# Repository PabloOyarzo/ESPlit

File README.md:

---
{}
---
# ESPlit

The ESPlit is an Ergonomic Split Keyboard based on the ESP32. Uses CHOC style switches, LiPo Battery and I2C connection through QWIC and TRRS connectors. 

[v0.2-alpha - KICAD Web view from KiCanvas](https://kicanvas.org/?github=https://github.com/PabloOyarzo/ESPlit/blob/f03de27275e5d2c74a1ab2e2412ca9cb5b31ff47/split_keyboard.kicad_pro)

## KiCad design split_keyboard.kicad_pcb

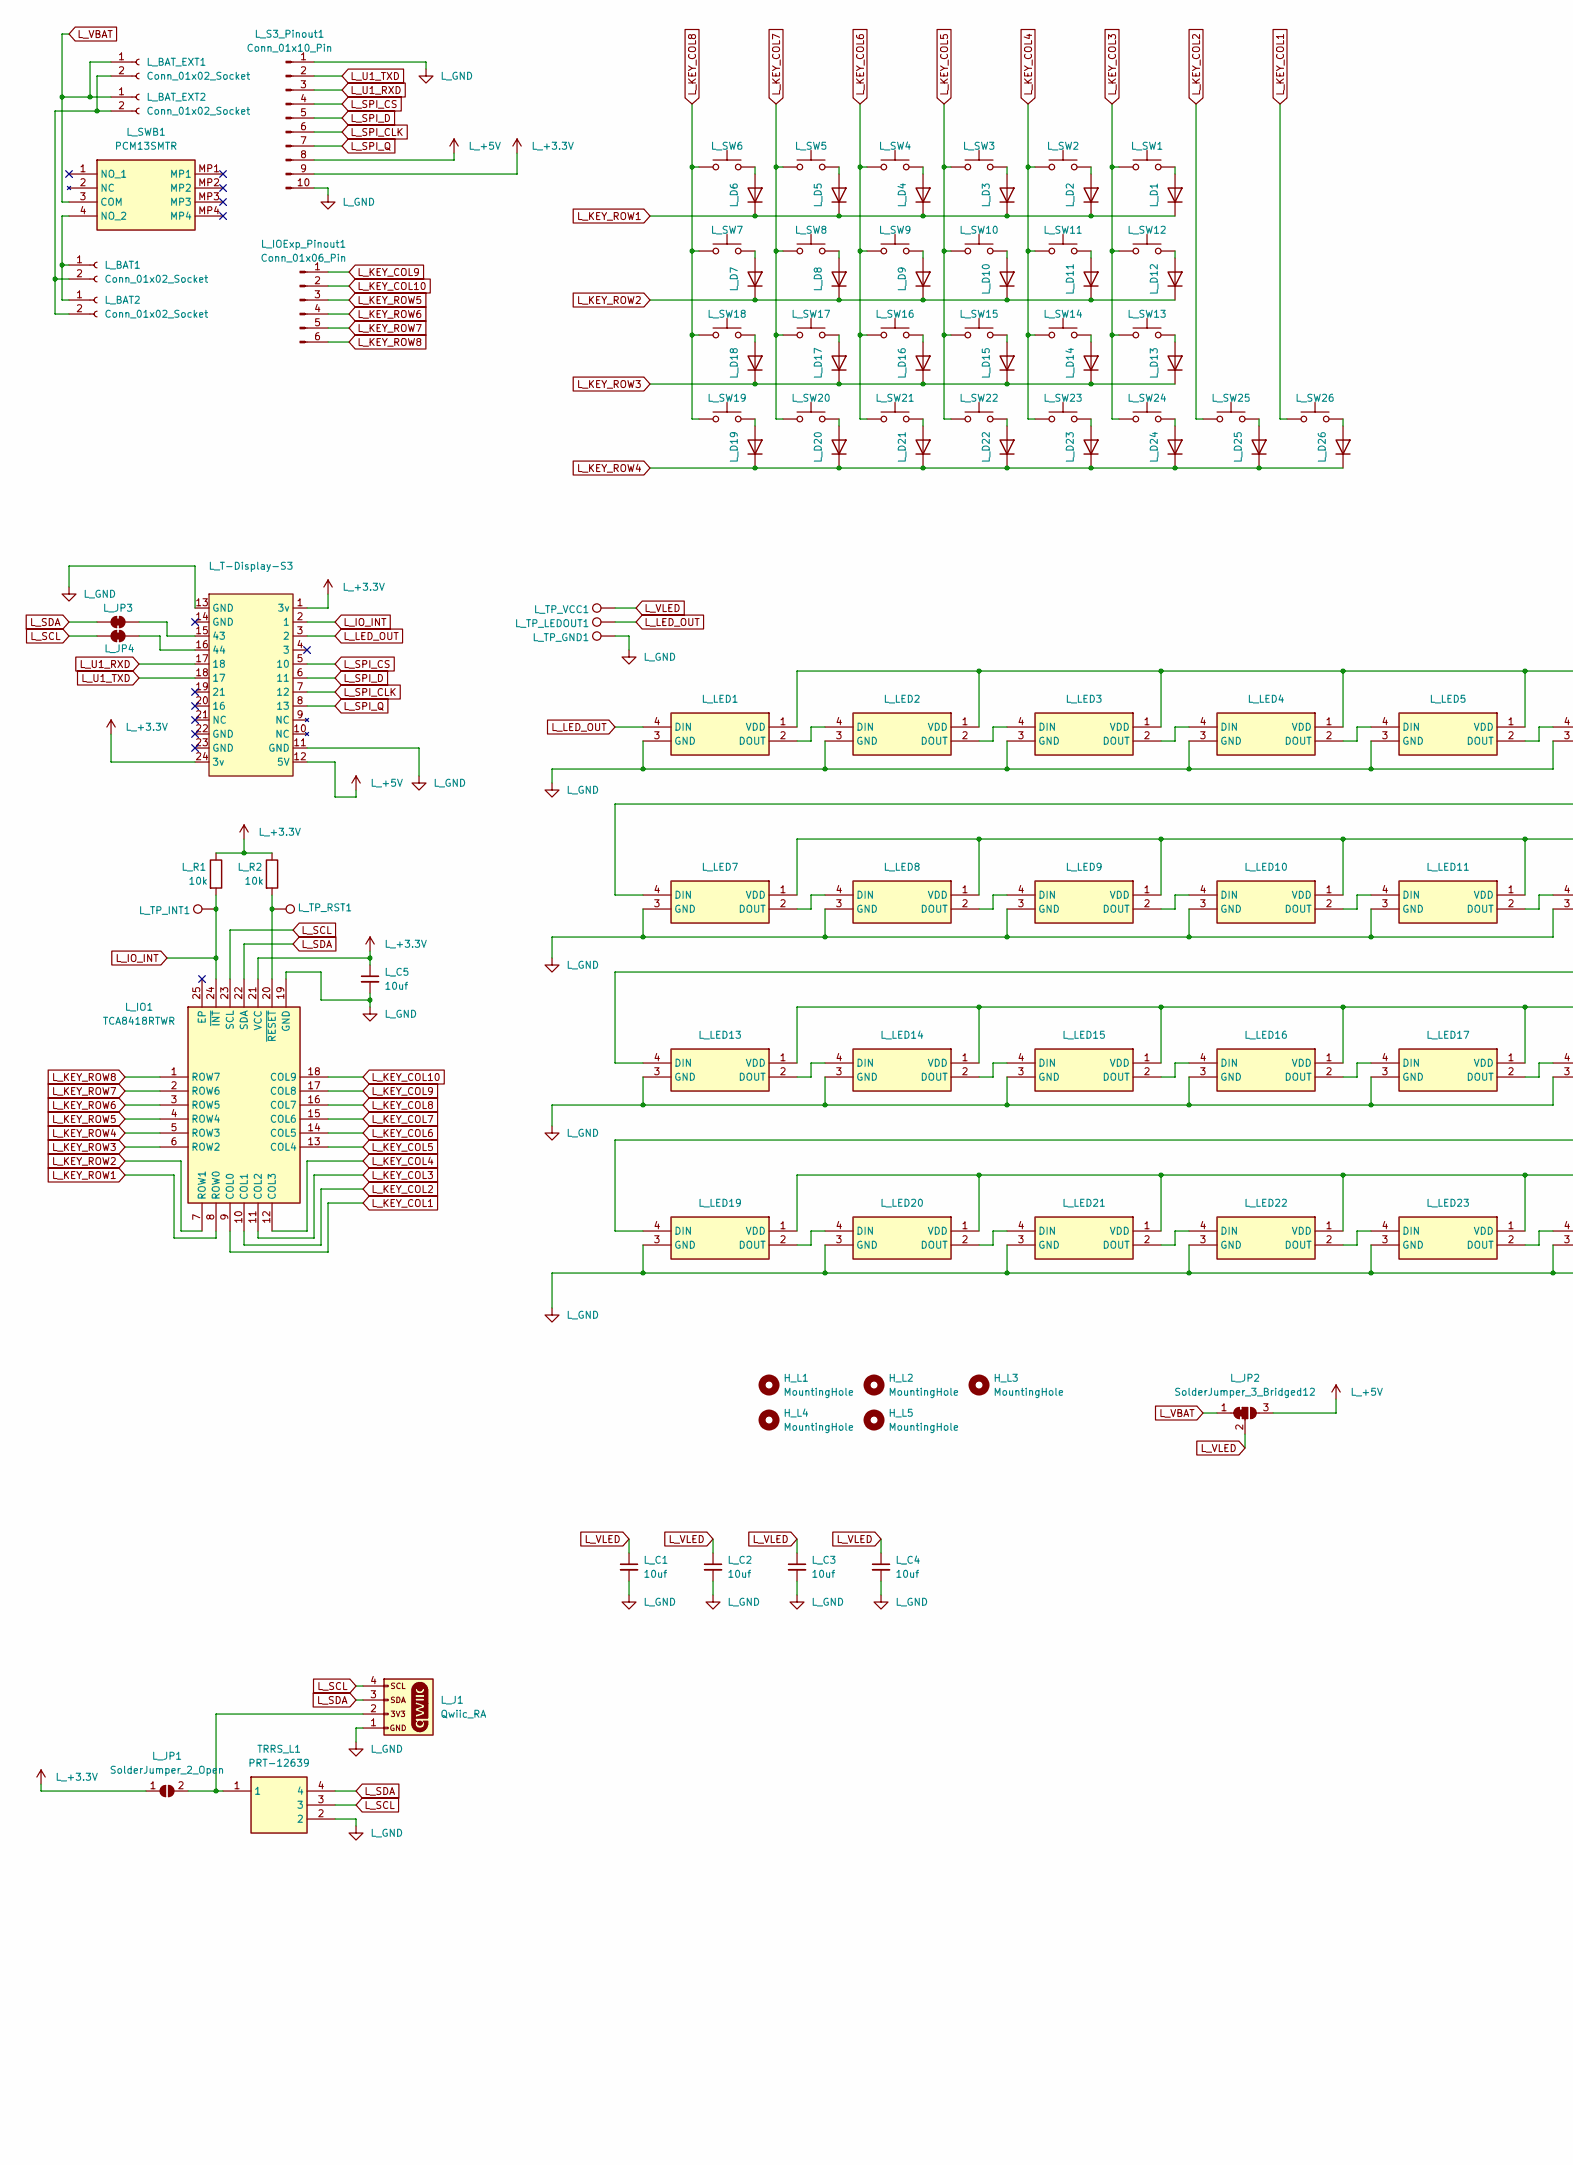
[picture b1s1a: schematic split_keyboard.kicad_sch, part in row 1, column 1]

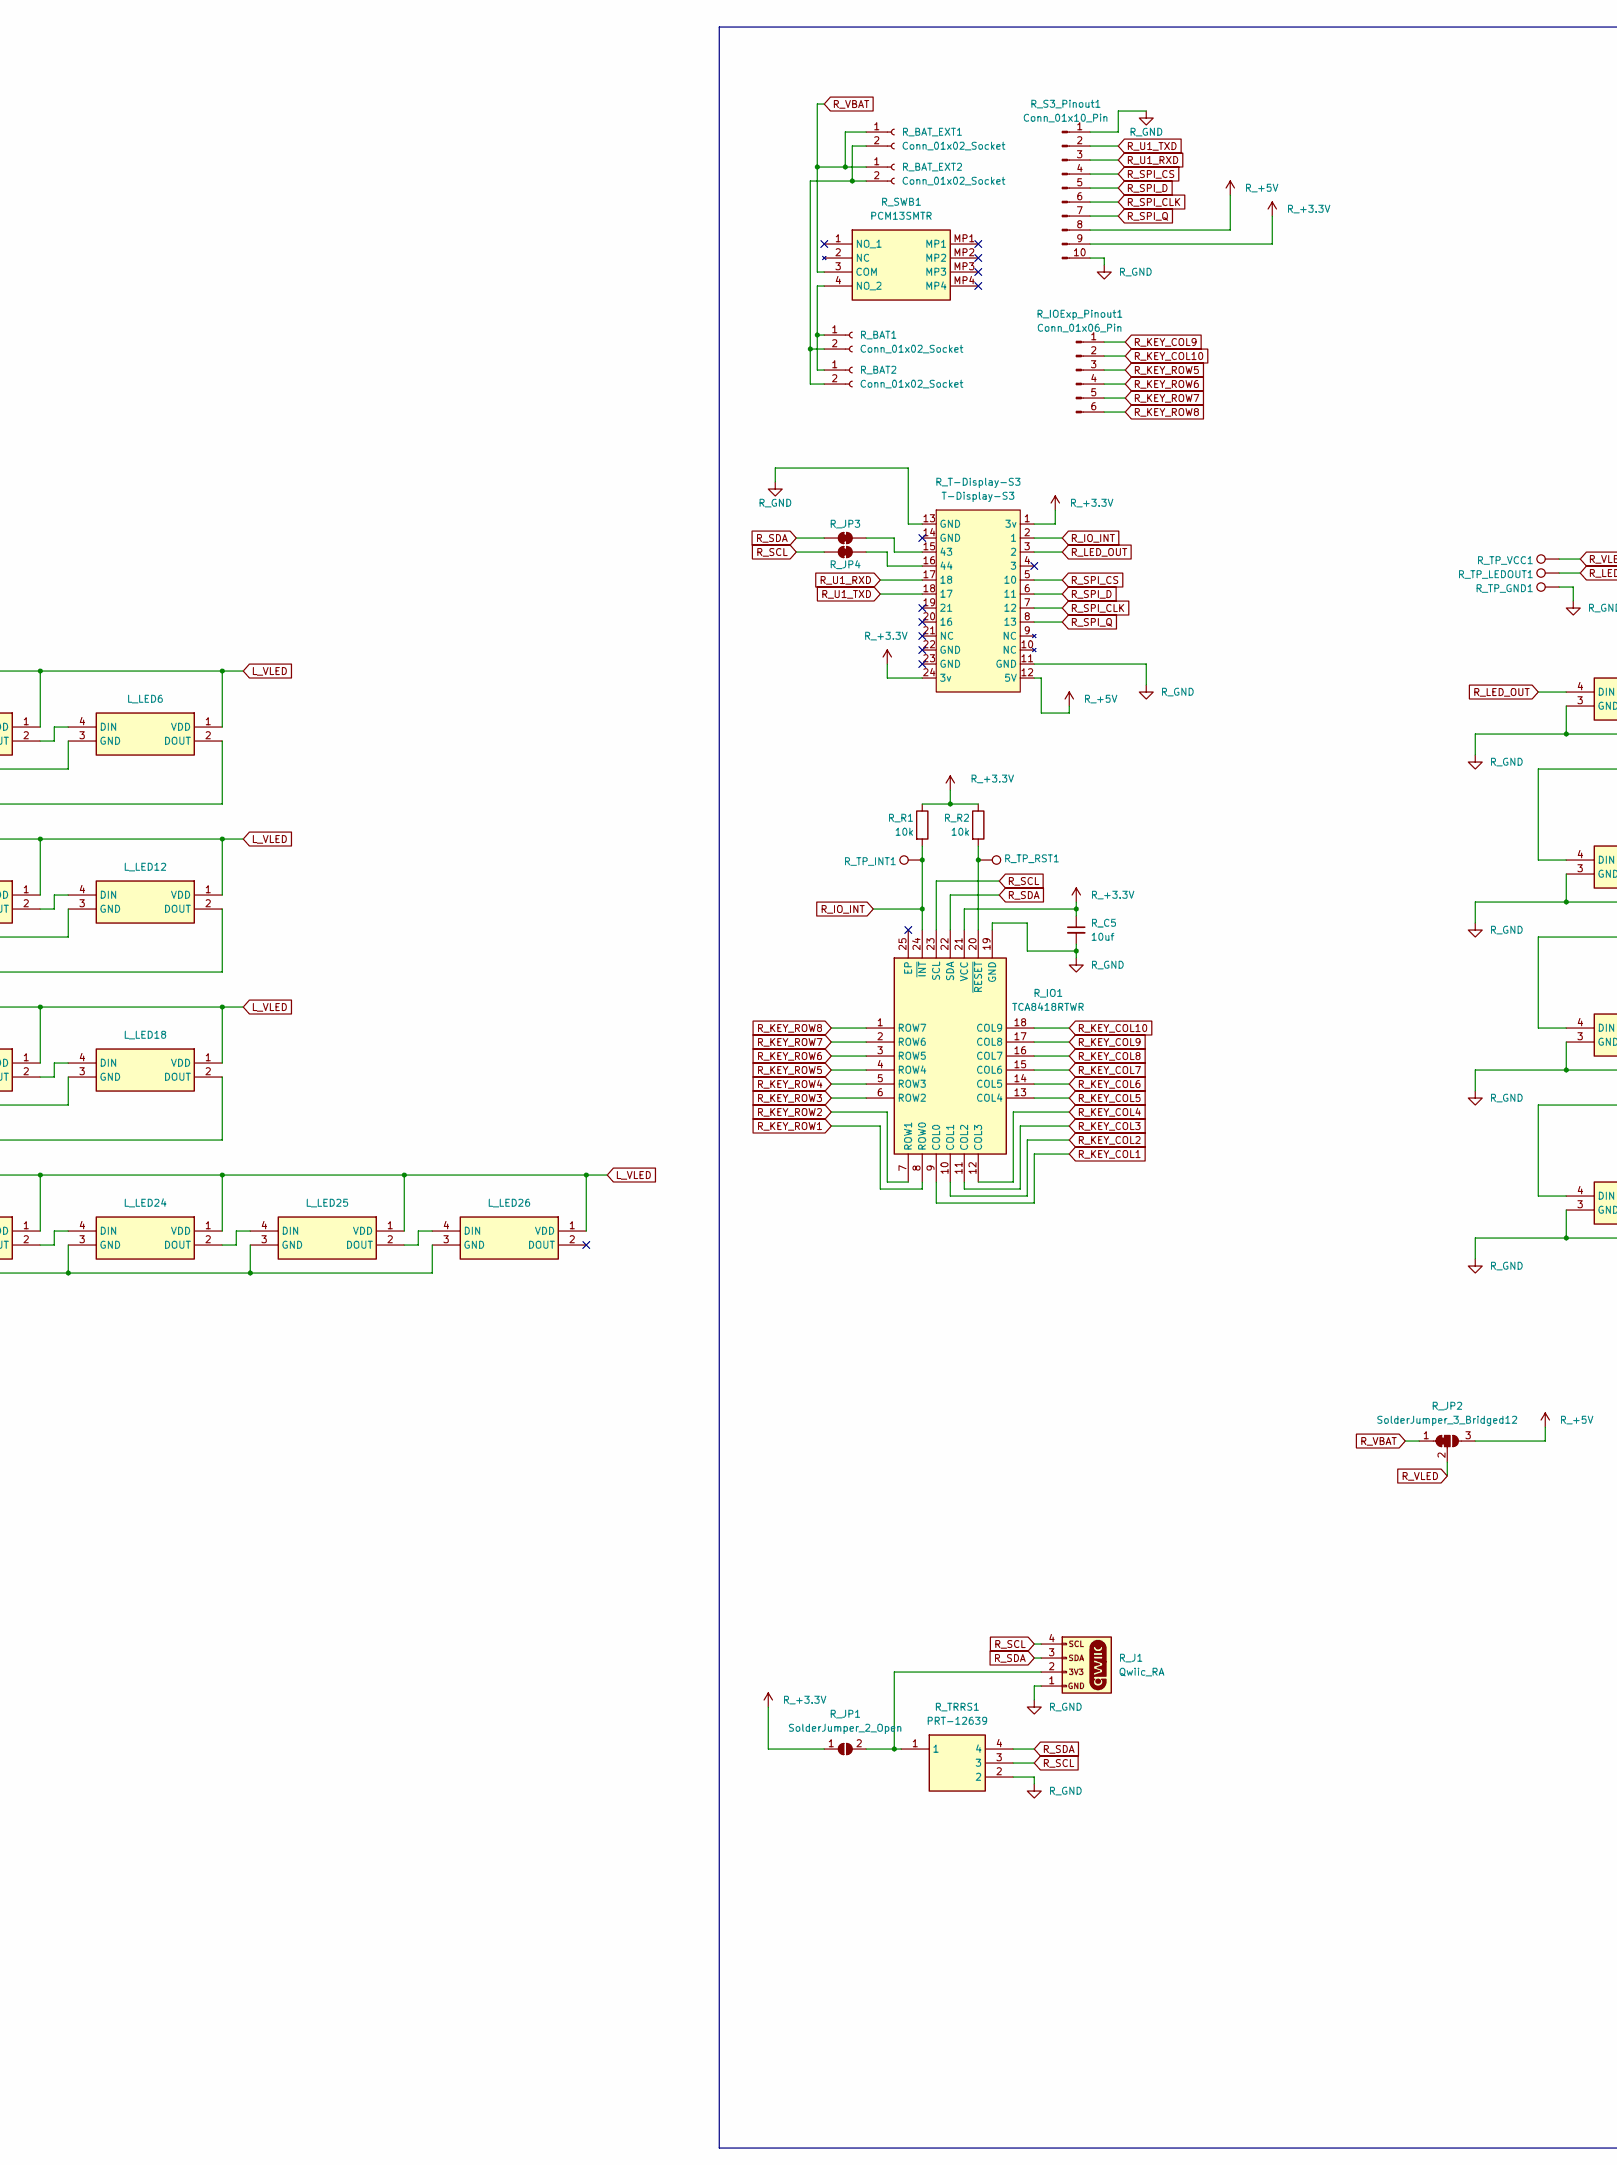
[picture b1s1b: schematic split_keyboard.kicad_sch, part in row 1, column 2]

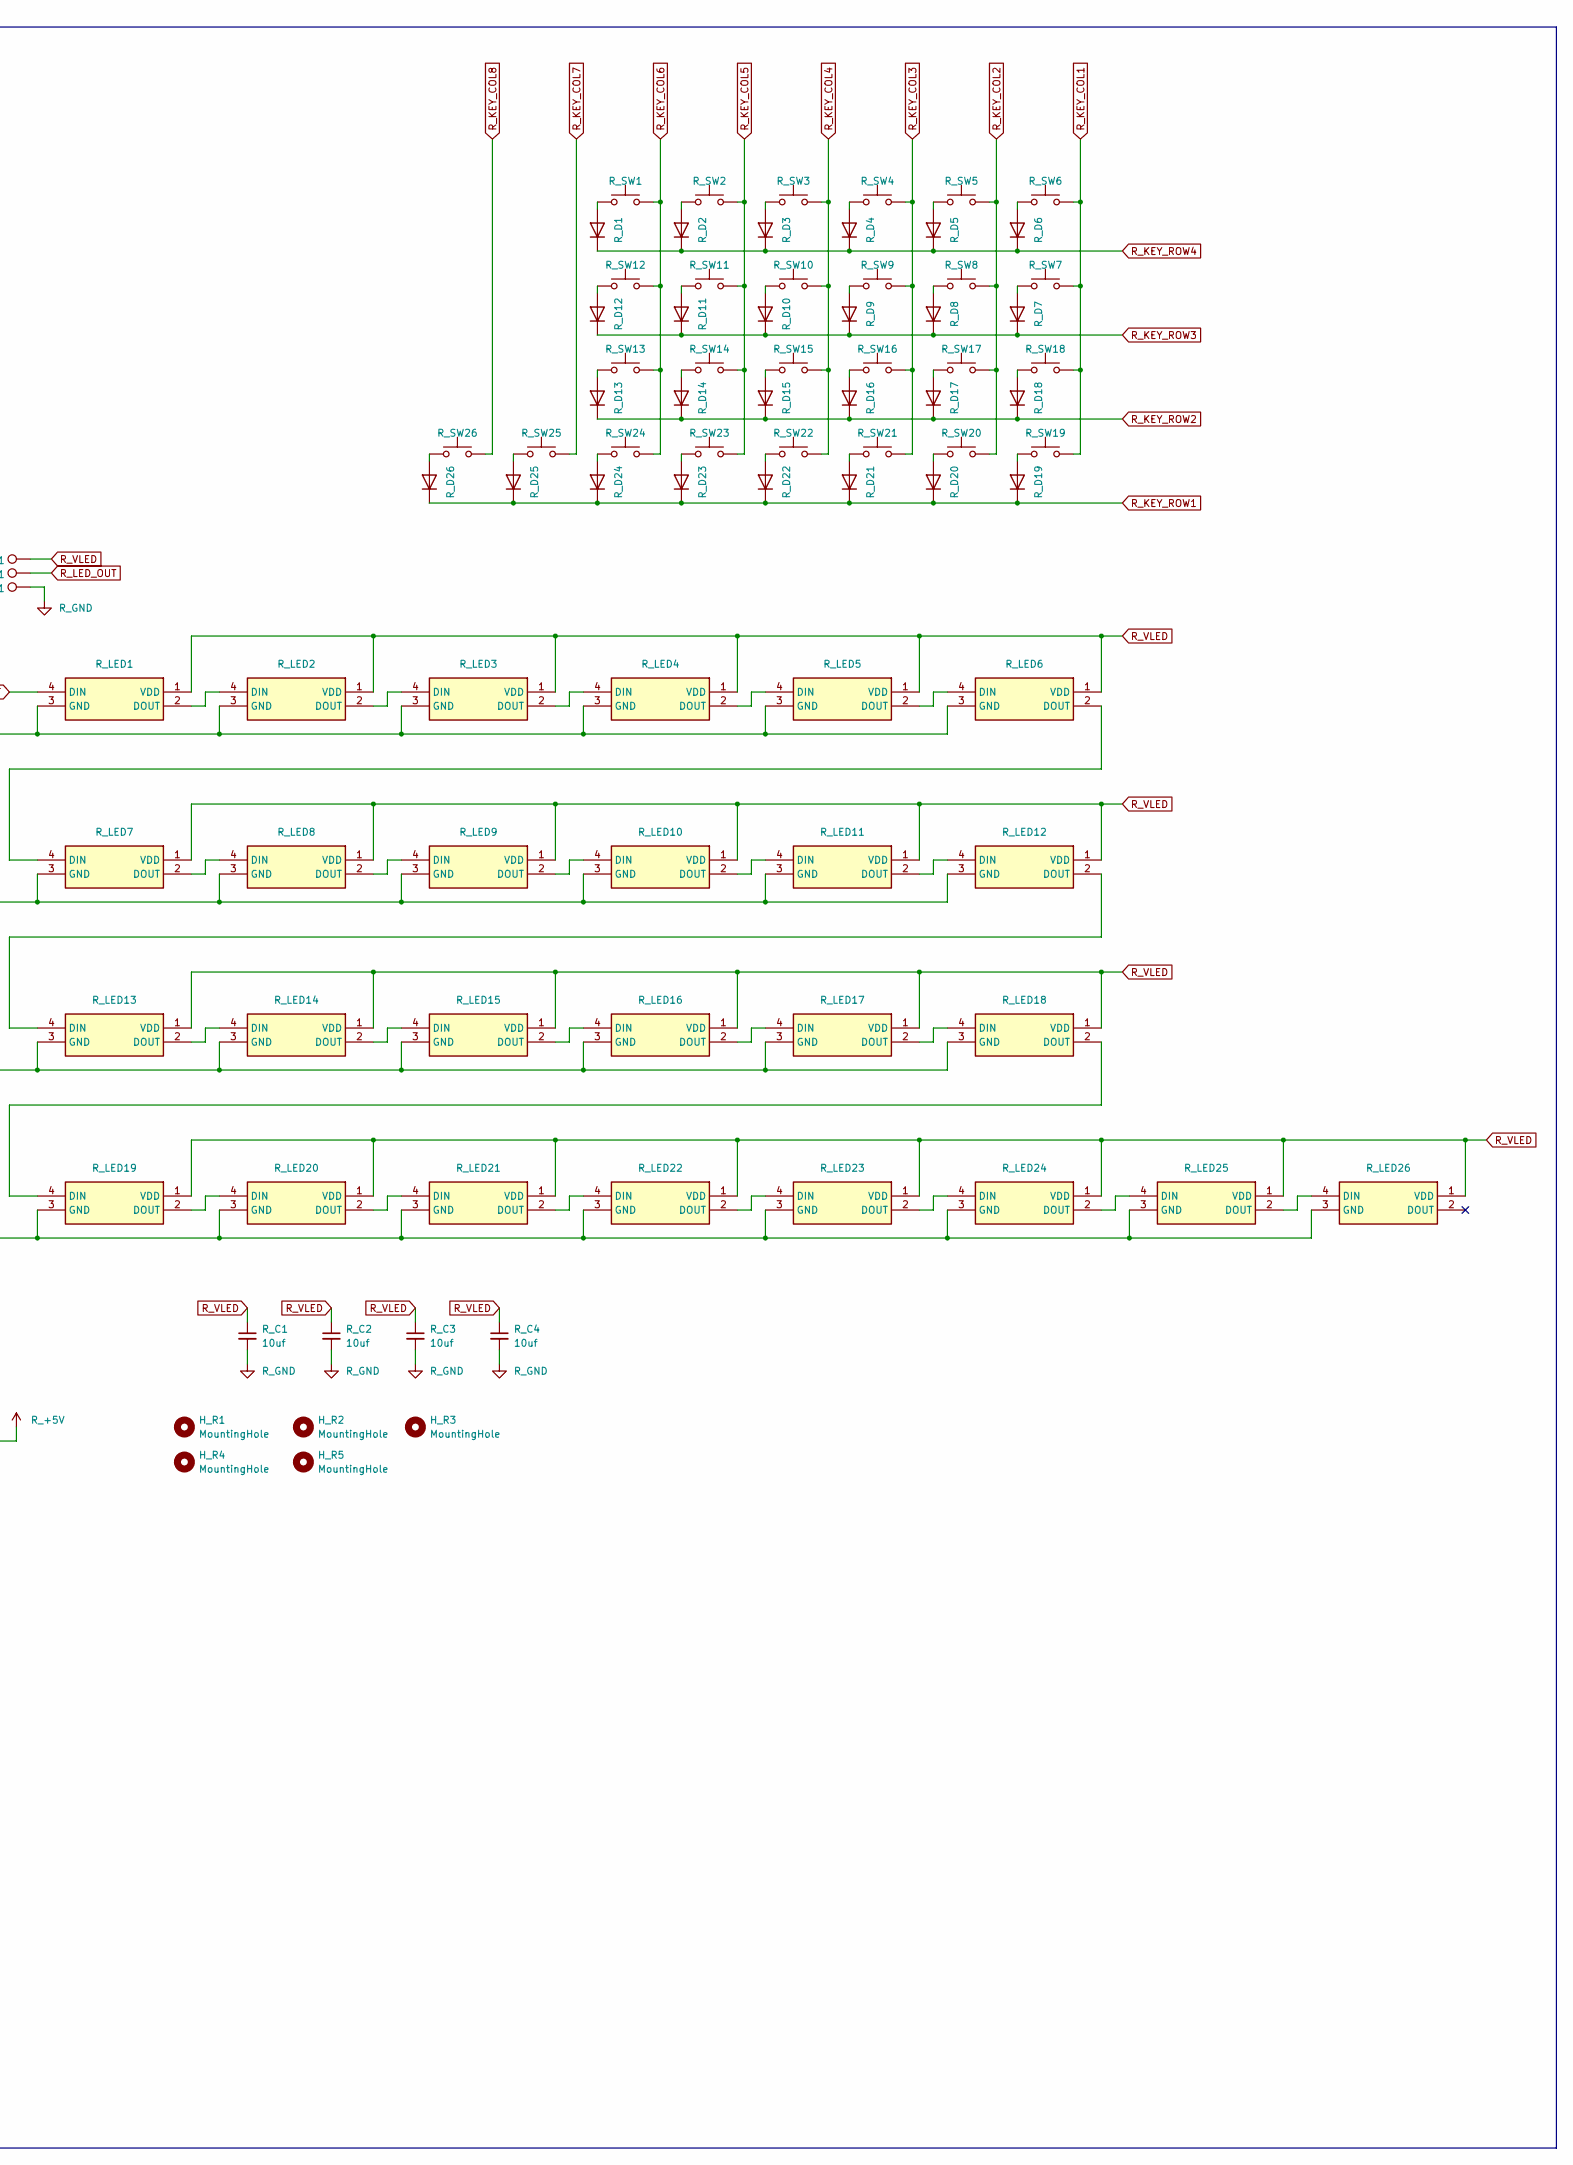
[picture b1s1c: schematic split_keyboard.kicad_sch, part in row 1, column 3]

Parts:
H_L1, H_L2, H_L3, H_L4, H_L5: MountingHole; MountingHole_2.5mm_Pad_TopBottom
H_R1, H_R2, H_R3, H_R4, H_R5: MountingHole; MountingHole_2.5mm_Pad_TopBottom
L_BAT1: Conn_01x02_Socket; JST_PH_B2B-PH-SM4-TB_02x2.00mm_Straight
L_BAT2: Conn_01x02_Socket; JST_GH_BM02B-GHS-TBT_02x1.25mm_Straight
L_BAT_EXT1: Conn_01x02_Socket; JST_PH_B2B-PH-SM4-TB_02x2.00mm_Straight
L_BAT_EXT2: Conn_01x02_Socket; PinHeader_1x02_P2.54mm_Vertical
L_C1, L_C2, L_C3, L_C4, L_C5: 10uf; C_0805_2012Metric
L_D1, L_D2, L_D3, L_D4, L_D5, L_D6, L_D7, L_D8, L_D9, L_D10, L_D11, L_D12, L_D13, L_D14, L_D15, L_D16, L_D17, L_D18, L_D19, L_D20, L_D21, L_D22, L_D23, L_D24, L_D25, L_D26: D; D_0805
L_IO1: TCA8418RTWR; QFN50P400X400X80-25N; Manufacturer_Part_Number TCA8418RTWR
L_IOExp_Pinout1: Conn_01x06_Pin; PinHeader_1x06_P2.54mm_Vertical
L_J1: Qwiic_RA; JST_SMD_1.0mm-4_RA
L_JP1: SolderJumper_2_Open; SolderJumper-2_P1.3mm_Open_TrianglePad1.0x1.5mm
L_JP2: SolderJumper_3_Bridged12; SolderJumper-3_P1.3mm_Bridged12_RoundedPad1.0x1.5mm
L_JP3, L_JP4: Measure; Jumper_2_NC_Trace_NoSilk
L_LED1, L_LED2, L_LED3, L_LED4, L_LED5, L_LED6, L_LED7, L_LED8, L_LED9, L_LED10, L_LED11, L_LED12, L_LED13, L_LED14, L_LED15, L_LED16, L_LED17, L_LED18, L_LED19, L_LED20, L_LED21, L_LED22, L_LED23, L_LED24, L_LED25, L_LED26: SK6812MINI-E; SK6812-MINI-E; Manufacturer_Part_Number SK6812MINI-E
L_R1, L_R2: 10k; R_0805_2012Metric
L_S3_Pinout1: Conn_01x10_Pin; PinHeader_1x10_P2.54mm_Vertical
L_SW1, L_SW2, L_SW3, L_SW4, L_SW5, L_SW6, L_SW7, L_SW8, L_SW9, L_SW10, L_SW11, L_SW12, L_SW13, L_SW14, L_SW15, L_SW16, L_SW17, L_SW18, L_SW19, L_SW20, L_SW21, L_SW22, L_SW23, L_SW24, L_SW25, L_SW26: L_SW; SW_Hotswap_Kailh_Choc_V1V2_Plated_1.00u
L_SWB1: PCM13SMTR; Manufacturer_Part_Number PCM13SMTR
L_T-Display-S3: T-Display-S3
L_TP_GND1: 1.25mm; TestPoint-1.25mm
L_TP_INT1: 1.25mm; TestPoint-1.25mm
L_TP_LEDOUT1: 1.25mm; TestPoint-1.25mm
L_TP_RST1: 1.25mm; TestPoint-1.25mm
L_TP_VCC1: 1.25mm; TestPoint-1.25mm
R_BAT1: Conn_01x02_Socket; JST_PH_B2B-PH-SM4-TB_02x2.00mm_Straight
R_BAT2: Conn_01x02_Socket; JST_GH_BM02B-GHS-TBT_02x1.25mm_Straight
R_BAT_EXT1: Conn_01x02_Socket; JST_PH_B2B-PH-SM4-TB_02x2.00mm_Straight
R_BAT_EXT2: Conn_01x02_Socket; PinHeader_1x02_P2.54mm_Vertical
R_C1, R_C2, R_C3, R_C4, R_C5: 10uf; C_0805_2012Metric
R_D1, R_D2, R_D3, R_D4, R_D5, R_D6, R_D7, R_D8, R_D9, R_D10, R_D11, R_D12, R_D13, R_D14, R_D15, R_D16, R_D17, R_D18, R_D19, R_D20, R_D21, R_D22, R_D23, R_D24, R_D25, R_D26: D; D_0805
R_IO1: TCA8418RTWR; QFN50P400X400X80-25N; Manufacturer_Part_Number TCA8418RTWR
R_IOExp_Pinout1: Conn_01x06_Pin; PinHeader_1x06_P2.54mm_Vertical
R_J1: Qwiic_RA; JST_SMD_1.0mm-4_RA
R_JP1: SolderJumper_2_Open; SolderJumper-2_P1.3mm_Open_TrianglePad1.0x1.5mm
R_JP2: SolderJumper_3_Bridged12; SolderJumper-3_P1.3mm_Bridged12_RoundedPad1.0x1.5mm
R_JP3, R_JP4: Measure; Jumper_2_NC_Trace_NoSilk
R_LED1, R_LED2, R_LED3, R_LED4, R_LED5, R_LED6, R_LED7, R_LED8, R_LED9, R_LED10, R_LED11, R_LED12, R_LED13, R_LED14, R_LED15, R_LED16, R_LED17, R_LED18, R_LED19, R_LED20, R_LED21, R_LED22, R_LED23, R_LED24, R_LED25, R_LED26: SK6812MINI-E; SK6812-MINI-E; Manufacturer_Part_Number SK6812MINI-E
R_R1, R_R2: 10k; R_0805_2012Metric
R_S3_Pinout1: Conn_01x10_Pin; PinHeader_1x10_P2.54mm_Vertical
R_SW1, R_SW2, R_SW3, R_SW4, R_SW5, R_SW6, R_SW7, R_SW8, R_SW9, R_SW10, R_SW11, R_SW12, R_SW13, R_SW14, R_SW15, R_SW16, R_SW17, R_SW18, R_SW19, R_SW20, R_SW21, R_SW22, R_SW23, R_SW24, R_SW25, R_SW26: L_SW; SW_Hotswap_Kailh_Choc_V1V2_Plated_1.00u
R_SWB1: PCM13SMTR; Manufacturer_Part_Number PCM13SMTR
R_T-Display-S3: T-Display-S3
R_TP_GND1: 1.25mm; TestPoint-1.25mm
R_TP_INT1: 1.25mm; TestPoint-1.25mm
R_TP_LEDOUT1: 1.25mm; TestPoint-1.25mm
R_TP_RST1: 1.25mm; TestPoint-1.25mm
R_TP_VCC1: 1.25mm; TestPoint-1.25mm
R_TRRS1: PRT-12639; TRRS-PJ-320A; Manufacturer_Part_Number PRT-12639
TRRS_L1: PRT-12639; TRRS-PJ-320A; Manufacturer_Part_Number PRT-12639

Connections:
L_+3.3V: L_C5.1, L_IO1.21 (VCC), L_JP1.1 (A), L_R1.1, L_R2.1, L_S3_Pinout1.9, L_T-Display-S3.1 (3v), L_T-Display-S3.24 (3v)
L_+5V: L_JP2.3 (B), L_S3_Pinout1.8, L_T-Display-S3.12 (5V)
L_GND: L_C1.2, L_C2.2, L_C3.2, L_C4.2, L_C5.2, L_IO1.19 (GND), L_J1.1, L_LED1.3 (GND), L_LED2.3 (GND), L_LED3.3 (GND), L_LED4.3 (GND), L_LED5.3 (GND), L_LED6.3 (GND), L_LED7.3 (GND), L_LED8.3 (GND), L_LED9.3 (GND), L_LED10.3 (GND), L_LED11.3 (GND), L_LED12.3 (GND), L_LED13.3 (GND), L_LED14.3 (GND), L_LED15.3 (GND), L_LED16.3 (GND), L_LED17.3 (GND), L_LED18.3 (GND), L_LED19.3 (GND), L_LED20.3 (GND), L_LED21.3 (GND), L_LED22.3 (GND), L_LED23.3 (GND), L_LED24.3 (GND), L_LED25.3 (GND), L_LED26.3 (GND), L_S3_Pinout1.1, L_S3_Pinout1.10, L_T-Display-S3.11 (GND), L_T-Display-S3.13 (GND), L_TP_GND1.1, TRRS_L1.2
L_IO_INT: L_IO1.24 (~INT), L_R1.2, L_T-Display-S3.2 (1), L_TP_INT1.1
L_KEY_COL1: L_IO1.9 (COL0), L_SW26.1
L_KEY_COL2: L_IO1.10 (COL1), L_SW25.1
L_KEY_COL3: L_IO1.11 (COL2), L_SW1.1, L_SW12.1, L_SW13.1, L_SW24.1
L_KEY_COL4: L_IO1.12 (COL3), L_SW2.1, L_SW11.1, L_SW14.1, L_SW23.1
L_KEY_COL5: L_IO1.13 (COL4), L_SW3.1, L_SW10.1, L_SW15.1, L_SW22.1
L_KEY_COL6: L_IO1.14 (COL5), L_SW4.1, L_SW9.1, L_SW16.1, L_SW21.1
L_KEY_COL7: L_IO1.15 (COL6), L_SW5.1, L_SW8.1, L_SW17.1, L_SW20.1
L_KEY_COL8: L_IO1.16 (COL7), L_SW6.1, L_SW7.1, L_SW18.1, L_SW19.1
L_KEY_COL9: L_IO1.17 (COL8), L_IOExp_Pinout1.1
L_KEY_COL10: L_IO1.18 (COL9), L_IOExp_Pinout1.2
L_KEY_ROW1: L_D1.1 (K), L_D2.1 (K), L_D3.1 (K), L_D4.1 (K), L_D5.1 (K), L_D6.1 (K), L_IO1.8 (ROW0)
L_KEY_ROW2: L_D7.1 (K), L_D8.1 (K), L_D9.1 (K), L_D10.1 (K), L_D11.1 (K), L_D12.1 (K), L_IO1.7 (ROW1)
L_KEY_ROW3: L_D13.1 (K), L_D14.1 (K), L_D15.1 (K), L_D16.1 (K), L_D17.1 (K), L_D18.1 (K), L_IO1.6 (ROW2)
L_KEY_ROW4: L_D19.1 (K), L_D20.1 (K), L_D21.1 (K), L_D22.1 (K), L_D23.1 (K), L_D24.1 (K), L_D25.1 (K), L_D26.1 (K), L_IO1.5 (ROW3)
L_KEY_ROW5: L_IO1.4 (ROW4), L_IOExp_Pinout1.3
L_KEY_ROW6: L_IO1.3 (ROW5), L_IOExp_Pinout1.4
L_KEY_ROW7: L_IO1.2 (ROW6), L_IOExp_Pinout1.5
L_KEY_ROW8: L_IO1.1 (ROW7), L_IOExp_Pinout1.6
L_LED_OUT: L_LED1.4 (DIN), L_T-Display-S3.3 (2), L_TP_LEDOUT1.1
L_SCL: L_IO1.23 (SCL), L_J1.4, L_JP4.1 (A), TRRS_L1.3
L_SDA: L_IO1.22 (SDA), L_J1.3, L_JP3.1 (A), TRRS_L1.4
L_SPI_CLK: L_S3_Pinout1.6, L_T-Display-S3.7 (12)
L_SPI_CS: L_S3_Pinout1.4, L_T-Display-S3.5 (10)
L_SPI_D: L_S3_Pinout1.5, L_T-Display-S3.6 (11)
L_SPI_Q: L_S3_Pinout1.7, L_T-Display-S3.8 (13)
L_U1_RXD: L_S3_Pinout1.3, L_T-Display-S3.17 (18)
L_U1_TXD: L_S3_Pinout1.2, L_T-Display-S3.18 (17)
L_VBAT: L_BAT_EXT1.1, L_BAT_EXT2.1, L_JP2.1 (A), L_SWB1.3 (COM)
L_VLED: L_C1.1, L_C2.1, L_C3.1, L_C4.1, L_JP2.2 (C), L_LED1.1 (VDD), L_LED2.1 (VDD), L_LED3.1 (VDD), L_LED4.1 (VDD), L_LED5.1 (VDD), L_LED6.1 (VDD), L_LED7.1 (VDD), L_LED8.1 (VDD), L_LED9.1 (VDD), L_LED10.1 (VDD), L_LED11.1 (VDD), L_LED12.1 (VDD), L_LED13.1 (VDD), L_LED14.1 (VDD), L_LED15.1 (VDD), L_LED16.1 (VDD), L_LED17.1 (VDD), L_LED18.1 (VDD), L_LED19.1 (VDD), L_LED20.1 (VDD), L_LED21.1 (VDD), L_LED22.1 (VDD), L_LED23.1 (VDD), L_LED24.1 (VDD), L_LED25.1 (VDD), L_LED26.1 (VDD), L_TP_VCC1.1
unnamed: L_BAT1.1, L_BAT2.1, L_SWB1.4 (NO_2)
unnamed: L_BAT1.2, L_BAT2.2, L_BAT_EXT1.2, L_BAT_EXT2.2
unnamed: L_D1.2 (A), L_SW1.2
unnamed: L_D2.2 (A), L_SW2.2
unnamed: L_D3.2 (A), L_SW3.2
unnamed: L_D4.2 (A), L_SW4.2
unnamed: L_D5.2 (A), L_SW5.2
unnamed: L_D6.2 (A), L_SW6.2
unnamed: L_D7.2 (A), L_SW7.2
unnamed: L_D8.2 (A), L_SW8.2
unnamed: L_D9.2 (A), L_SW9.2
unnamed: L_D10.2 (A), L_SW10.2
unnamed: L_D11.2 (A), L_SW11.2
unnamed: L_D12.2 (A), L_SW12.2
unnamed: L_D13.2 (A), L_SW13.2
unnamed: L_D14.2 (A), L_SW14.2
unnamed: L_D15.2 (A), L_SW15.2
unnamed: L_D16.2 (A), L_SW16.2
unnamed: L_D17.2 (A), L_SW17.2
unnamed: L_D18.2 (A), L_SW18.2
unnamed: L_D19.2 (A), L_SW19.2
unnamed: L_D20.2 (A), L_SW20.2
unnamed: L_D21.2 (A), L_SW21.2
unnamed: L_D22.2 (A), L_SW22.2
unnamed: L_D23.2 (A), L_SW23.2
unnamed: L_D24.2 (A), L_SW24.2
unnamed: L_D25.2 (A), L_SW25.2
unnamed: L_D26.2 (A), L_SW26.2
unnamed: L_IO1.20 (~RESET), L_R2.2, L_TP_RST1.1
unnamed: L_J1.2, L_JP1.2 (B), TRRS_L1.1
unnamed: L_JP3.2 (B), L_T-Display-S3.15 (43)
unnamed: L_JP4.2 (B), L_T-Display-S3.16 (44)
unnamed: L_LED1.2 (DOUT), L_LED2.4 (DIN)
unnamed: L_LED2.2 (DOUT), L_LED3.4 (DIN)
unnamed: L_LED3.2 (DOUT), L_LED4.4 (DIN)
unnamed: L_LED4.2 (DOUT), L_LED5.4 (DIN)
unnamed: L_LED5.2 (DOUT), L_LED6.4 (DIN)
unnamed: L_LED6.2 (DOUT), L_LED7.4 (DIN)
unnamed: L_LED7.2 (DOUT), L_LED8.4 (DIN)
unnamed: L_LED8.2 (DOUT), L_LED9.4 (DIN)
unnamed: L_LED9.2 (DOUT), L_LED10.4 (DIN)
unnamed: L_LED10.2 (DOUT), L_LED11.4 (DIN)
unnamed: L_LED11.2 (DOUT), L_LED12.4 (DIN)
unnamed: L_LED12.2 (DOUT), L_LED13.4 (DIN)
unnamed: L_LED13.2 (DOUT), L_LED14.4 (DIN)
unnamed: L_LED14.2 (DOUT), L_LED15.4 (DIN)
unnamed: L_LED15.2 (DOUT), L_LED16.4 (DIN)
unnamed: L_LED16.2 (DOUT), L_LED17.4 (DIN)
unnamed: L_LED17.2 (DOUT), L_LED18.4 (DIN)
unnamed: L_LED18.2 (DOUT), L_LED19.4 (DIN)
unnamed: L_LED19.2 (DOUT), L_LED20.4 (DIN)
unnamed: L_LED20.2 (DOUT), L_LED21.4 (DIN)
unnamed: L_LED21.2 (DOUT), L_LED22.4 (DIN)
unnamed: L_LED22.2 (DOUT), L_LED23.4 (DIN)
unnamed: L_LED23.2 (DOUT), L_LED24.4 (DIN)
unnamed: L_LED24.2 (DOUT), L_LED25.4 (DIN)
unnamed: L_LED25.2 (DOUT), L_LED26.4 (DIN)
unnamed: R_BAT1.1, R_BAT2.1, R_SWB1.4 (NO_2)
unnamed: R_BAT1.2, R_BAT2.2, R_BAT_EXT1.2, R_BAT_EXT2.2
unnamed: R_D1.2 (A), R_SW1.2
unnamed: R_D2.2 (A), R_SW2.2
unnamed: R_D3.2 (A), R_SW3.2
unnamed: R_D4.2 (A), R_SW4.2
unnamed: R_D5.2 (A), R_SW5.2
unnamed: R_D6.2 (A), R_SW6.2
unnamed: R_D7.2 (A), R_SW7.2
unnamed: R_D8.2 (A), R_SW8.2
unnamed: R_D9.2 (A), R_SW9.2
unnamed: R_D10.2 (A), R_SW10.2
unnamed: R_D11.2 (A), R_SW11.2
unnamed: R_D12.2 (A), R_SW12.2
unnamed: R_D13.2 (A), R_SW13.2
unnamed: R_D14.2 (A), R_SW14.2
unnamed: R_D15.2 (A), R_SW15.2
unnamed: R_D16.2 (A), R_SW16.2
unnamed: R_D17.2 (A), R_SW17.2
unnamed: R_D18.2 (A), R_SW18.2
unnamed: R_D19.2 (A), R_SW19.2
unnamed: R_D20.2 (A), R_SW20.2
unnamed: R_D21.2 (A), R_SW21.2
unnamed: R_D22.2 (A), R_SW22.2
unnamed: R_D23.2 (A), R_SW23.2
unnamed: R_D24.2 (A), R_SW24.2
unnamed: R_D25.2 (A), R_SW25.2
unnamed: R_D26.2 (A), R_SW26.2
unnamed: R_IO1.20 (~RESET), R_R2.2, R_TP_RST1.1
unnamed: R_J1.2, R_JP1.2 (B), R_TRRS1.1
unnamed: R_JP3.2 (B), R_T-Display-S3.15 (43)
unnamed: R_JP4.2 (B), R_T-Display-S3.16 (44)
unnamed: R_LED1.2 (DOUT), R_LED2.4 (DIN)
unnamed: R_LED2.2 (DOUT), R_LED3.4 (DIN)
unnamed: R_LED3.2 (DOUT), R_LED4.4 (DIN)
unnamed: R_LED4.2 (DOUT), R_LED5.4 (DIN)
unnamed: R_LED5.2 (DOUT), R_LED6.4 (DIN)
unnamed: R_LED6.2 (DOUT), R_LED7.4 (DIN)
unnamed: R_LED7.2 (DOUT), R_LED8.4 (DIN)
unnamed: R_LED8.2 (DOUT), R_LED9.4 (DIN)
unnamed: R_LED9.2 (DOUT), R_LED10.4 (DIN)
unnamed: R_LED10.2 (DOUT), R_LED11.4 (DIN)
unnamed: R_LED11.2 (DOUT), R_LED12.4 (DIN)
unnamed: R_LED12.2 (DOUT), R_LED13.4 (DIN)
unnamed: R_LED13.2 (DOUT), R_LED14.4 (DIN)
unnamed: R_LED14.2 (DOUT), R_LED15.4 (DIN)
unnamed: R_LED15.2 (DOUT), R_LED16.4 (DIN)
unnamed: R_LED16.2 (DOUT), R_LED17.4 (DIN)
unnamed: R_LED17.2 (DOUT), R_LED18.4 (DIN)
unnamed: R_LED18.2 (DOUT), R_LED19.4 (DIN)
unnamed: R_LED19.2 (DOUT), R_LED20.4 (DIN)
unnamed: R_LED20.2 (DOUT), R_LED21.4 (DIN)
unnamed: R_LED21.2 (DOUT), R_LED22.4 (DIN)
unnamed: R_LED22.2 (DOUT), R_LED23.4 (DIN)
unnamed: R_LED23.2 (DOUT), R_LED24.4 (DIN)
unnamed: R_LED24.2 (DOUT), R_LED25.4 (DIN)
unnamed: R_LED25.2 (DOUT), R_LED26.4 (DIN)
R_+3.3V: R_C5.1, R_IO1.21 (VCC), R_JP1.1 (A), R_R1.1, R_R2.1, R_S3_Pinout1.9, R_T-Display-S3.1 (3v), R_T-Display-S3.24 (3v)
R_+5V: R_JP2.3 (B), R_S3_Pinout1.8, R_T-Display-S3.12 (5V)
R_GND: R_C1.2, R_C2.2, R_C3.2, R_C4.2, R_C5.2, R_IO1.19 (GND), R_J1.1, R_LED1.3 (GND), R_LED2.3 (GND), R_LED3.3 (GND), R_LED4.3 (GND), R_LED5.3 (GND), R_LED6.3 (GND), R_LED7.3 (GND), R_LED8.3 (GND), R_LED9.3 (GND), R_LED10.3 (GND), R_LED11.3 (GND), R_LED12.3 (GND), R_LED13.3 (GND), R_LED14.3 (GND), R_LED15.3 (GND), R_LED16.3 (GND), R_LED17.3 (GND), R_LED18.3 (GND), R_LED19.3 (GND), R_LED20.3 (GND), R_LED21.3 (GND), R_LED22.3 (GND), R_LED23.3 (GND), R_LED24.3 (GND), R_LED25.3 (GND), R_LED26.3 (GND), R_S3_Pinout1.1, R_S3_Pinout1.10, R_T-Display-S3.11 (GND), R_T-Display-S3.13 (GND), R_TP_GND1.1, R_TRRS1.2
R_IO_INT: R_IO1.24 (~INT), R_R1.2, R_T-Display-S3.2 (1), R_TP_INT1.1
R_KEY_COL1: R_IO1.9 (COL0), R_SW6.1, R_SW7.1, R_SW18.1, R_SW19.1
R_KEY_COL2: R_IO1.10 (COL1), R_SW5.1, R_SW8.1, R_SW17.1, R_SW20.1
R_KEY_COL3: R_IO1.11 (COL2), R_SW4.1, R_SW9.1, R_SW16.1, R_SW21.1
R_KEY_COL4: R_IO1.12 (COL3), R_SW3.1, R_SW10.1, R_SW15.1, R_SW22.1
R_KEY_COL5: R_IO1.13 (COL4), R_SW2.1, R_SW11.1, R_SW14.1, R_SW23.1
R_KEY_COL6: R_IO1.14 (COL5), R_SW1.1, R_SW12.1, R_SW13.1, R_SW24.1
R_KEY_COL7: R_IO1.15 (COL6), R_SW25.1
R_KEY_COL8: R_IO1.16 (COL7), R_SW26.1
R_KEY_COL9: R_IO1.17 (COL8), R_IOExp_Pinout1.1
R_KEY_COL10: R_IO1.18 (COL9), R_IOExp_Pinout1.2
R_KEY_ROW1: R_D19.1 (K), R_D20.1 (K), R_D21.1 (K), R_D22.1 (K), R_D23.1 (K), R_D24.1 (K), R_D25.1 (K), R_D26.1 (K), R_IO1.8 (ROW0)
R_KEY_ROW2: R_D13.1 (K), R_D14.1 (K), R_D15.1 (K), R_D16.1 (K), R_D17.1 (K), R_D18.1 (K), R_IO1.7 (ROW1)
R_KEY_ROW3: R_D7.1 (K), R_D8.1 (K), R_D9.1 (K), R_D10.1 (K), R_D11.1 (K), R_D12.1 (K), R_IO1.6 (ROW2)
R_KEY_ROW4: R_D1.1 (K), R_D2.1 (K), R_D3.1 (K), R_D4.1 (K), R_D5.1 (K), R_D6.1 (K), R_IO1.5 (ROW3)
R_KEY_ROW5: R_IO1.4 (ROW4), R_IOExp_Pinout1.3
R_KEY_ROW6: R_IO1.3 (ROW5), R_IOExp_Pinout1.4
R_KEY_ROW7: R_IO1.2 (ROW6), R_IOExp_Pinout1.5
R_KEY_ROW8: R_IO1.1 (ROW7), R_IOExp_Pinout1.6
R_LED_OUT: R_LED1.4 (DIN), R_T-Display-S3.3 (2), R_TP_LEDOUT1.1
R_SCL: R_IO1.23 (SCL), R_J1.4, R_JP4.1 (A), R_TRRS1.3
R_SDA: R_IO1.22 (SDA), R_J1.3, R_JP3.1 (A), R_TRRS1.4
R_SPI_CLK: R_S3_Pinout1.6, R_T-Display-S3.7 (12)
R_SPI_CS: R_S3_Pinout1.4, R_T-Display-S3.5 (10)
R_SPI_D: R_S3_Pinout1.5, R_T-Display-S3.6 (11)
R_SPI_Q: R_S3_Pinout1.7, R_T-Display-S3.8 (13)
R_U1_RXD: R_S3_Pinout1.3, R_T-Display-S3.17 (18)
R_U1_TXD: R_S3_Pinout1.2, R_T-Display-S3.18 (17)
R_VBAT: R_BAT_EXT1.1, R_BAT_EXT2.1, R_JP2.1 (A), R_SWB1.3 (COM)
R_VLED: R_C1.1, R_C2.1, R_C3.1, R_C4.1, R_JP2.2 (C), R_LED1.1 (VDD), R_LED2.1 (VDD), R_LED3.1 (VDD), R_LED4.1 (VDD), R_LED5.1 (VDD), R_LED6.1 (VDD), R_LED7.1 (VDD), R_LED8.1 (VDD), R_LED9.1 (VDD), R_LED10.1 (VDD), R_LED11.1 (VDD), R_LED12.1 (VDD), R_LED13.1 (VDD), R_LED14.1 (VDD), R_LED15.1 (VDD), R_LED16.1 (VDD), R_LED17.1 (VDD), R_LED18.1 (VDD), R_LED19.1 (VDD), R_LED20.1 (VDD), R_LED21.1 (VDD), R_LED22.1 (VDD), R_LED23.1 (VDD), R_LED24.1 (VDD), R_LED25.1 (VDD), R_LED26.1 (VDD), R_TP_VCC1.1

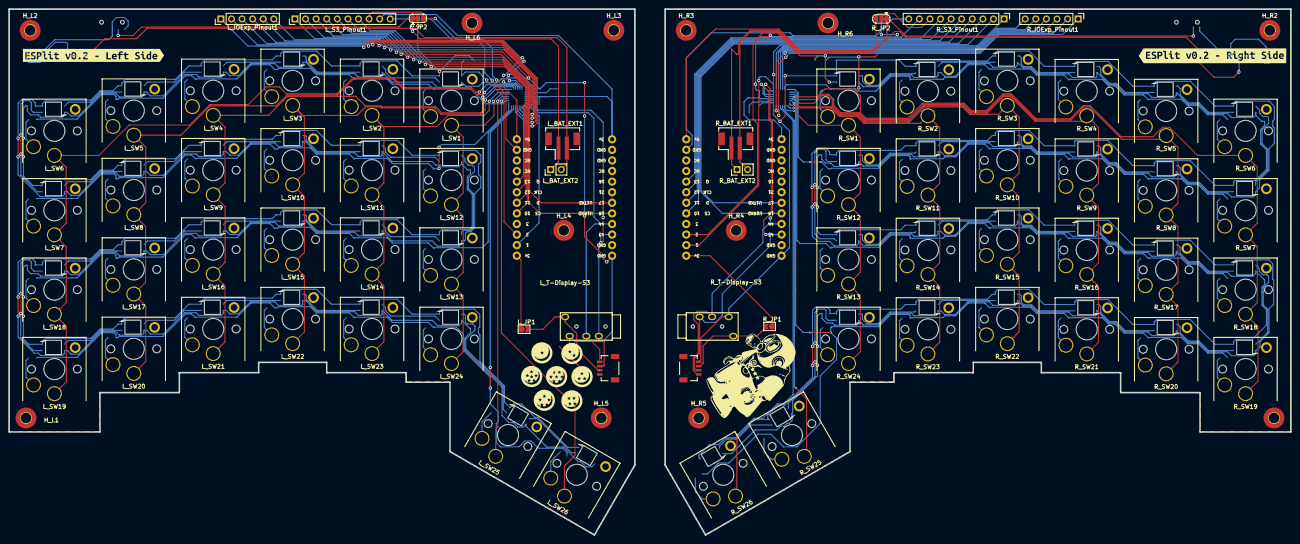
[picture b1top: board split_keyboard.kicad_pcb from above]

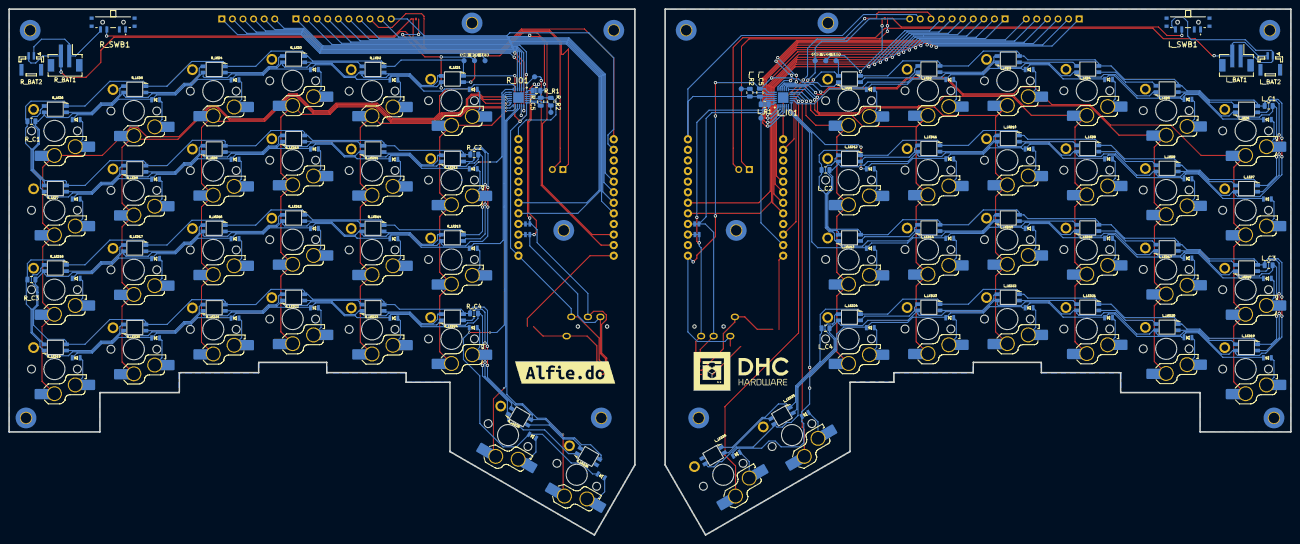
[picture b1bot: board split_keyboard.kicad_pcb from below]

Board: 2 copper layers, 307.5 x 126.2 mm, 227 parts (91 on the bottom side), 180 nets.

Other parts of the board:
H_L6: MountingHole; MountingHole_2.5mm_Pad_TopBottom
H_R6: MountingHole; MountingHole_2.5mm_Pad_TopBottom
kibuzzard-65EF74B4, kibuzzard-65EF74B4#2: G***; kibuzzard-65EF74B4
kibuzzard-6602E1CF: G***; kibuzzard-6602E1CF
kibuzzard-6603142B: G***; kibuzzard-6603142B
kibuzzard-6603143E: G***; kibuzzard-6603143E

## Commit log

2024-01-30 Init Commit
2024-01-30 Cleaning Libs
2024-02-01 adding readme
2024-02-01 Changed size of pcb page
2024-02-01 - Made a custom form of the key - Brang back the MINI-E lib, it was used for sch
2024-02-05 - Changed files for next version's keyboard layout - Added instructions on how to use kb's layout file - Modified a bit the LED footprint - Modified all names for symbols and part inside the pcb and 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
2024-02-05 - Added quick link for KiCanvas
2024-02-06 - Routed most of diode-switch-caps tracks
2024-02-08 - Positioned MCU and added documentation - Locked MCU's and keys
2024-02-11 - Moved most of the pieces from the old design to the new one
2024-02-11 - Located with exact coordinates the footprints moved.
2024-02-15 added more components and fix some in sch
2024-02-21 Right side almost done
2024-02-26 -Almost done
2024-02-27 added outline and holes
2024-02-27 holes located, kinda ready to send to production
2024-03-13 Added all TPs
2024-03-13 Finished board with plates done.
2024-03-13 deleting some files and added gitignore
2024-03-13 .gitignore is now working
2024-03-26 Added images and logo
2024-03-26 Added images to silkscreen
2024-04-07 commiting changes before change of name
2024-04-08 Made changes to ESPlit\README.md
2024-04-08 Revert "Made changes to ESPlit\README.md"
    This reverts commit a2da8ca64af4f9e2f3e5893288b205ac869bd5d7.
2024-04-08 fixed choc custom footprint ; added folders to gitignore
2024-04-13 Create LICENSE
2024-04-13 updated TODO
2024-04-13 cleaning up folders
2024-04-14 adding modify files for rebase
2024-04-14 Revert "adding modify files for rebase"
    This reverts commit d9b325c8eb764756efd70fe29d2c4224bc6c1de6.
2024-04-15 modified todo
